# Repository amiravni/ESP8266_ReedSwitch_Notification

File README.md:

# ESP8266_ReedSwitch_Notification

This is a repository for desining a PCB and code for creating an ESP8266 which can be kept alive for months and notify by email when the reed switch changing it state.

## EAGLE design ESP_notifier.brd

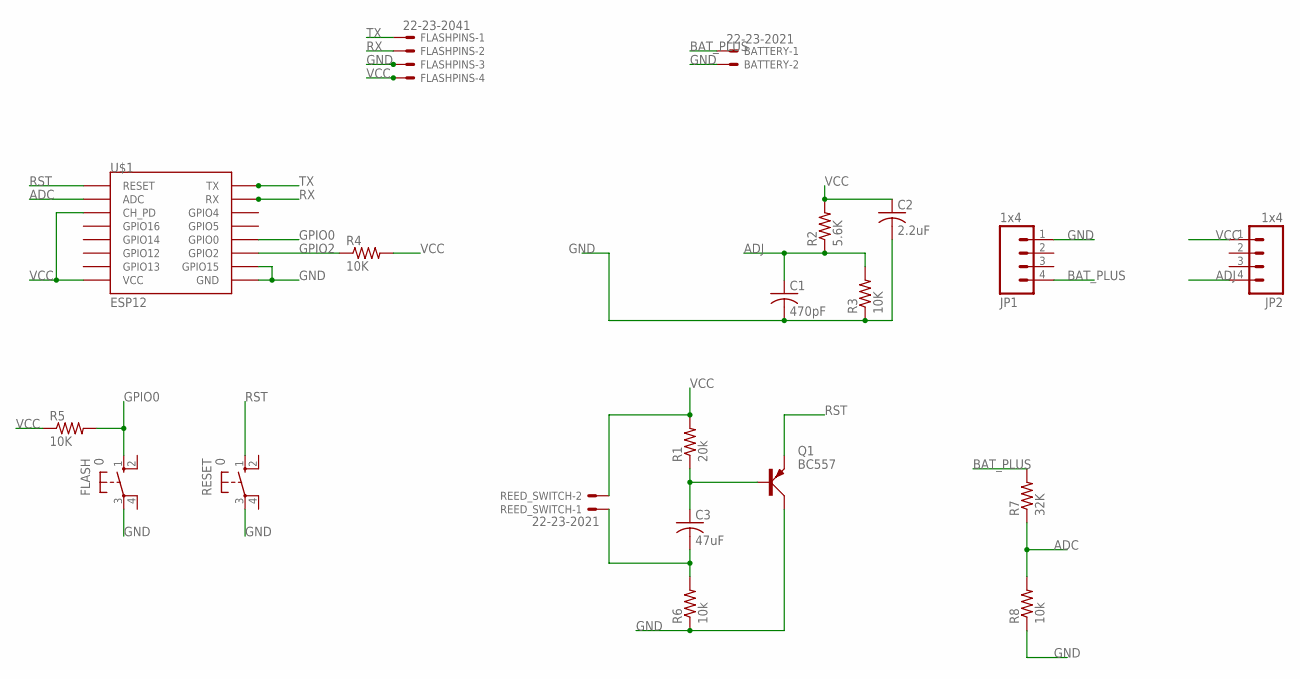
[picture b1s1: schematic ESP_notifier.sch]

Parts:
BATTERY: 22-23-2021
C1: 470pF; C075-032X103
C2: 2.2uF; C075-032X103
C3: 47uF; C075-032X103
FLASH: 0; B3F-10XX
FLASHPINS: 22-23-2041
JP1: 1x4; 1X04_NO_SILK
JP2: 1x4; 1X04_NO_SILK_ALL_ROUND
Q1: BC557; SOT54A
R1: 20k; 0207/9
R2: 5.6K; 0207/9
R3, R4, R5: 10K; 0207/9
R6, R8: 10k; 0207/9
R7: 32K; 0207/9
REED_SWITCH: 22-23-2021
RESET: 0; B3F-10XX
U$1: ESP12

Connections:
ADC: R7.1, R8.2, U$1.ADC
ADJ: C1.1, JP2.4, R2.1, R3.2
BAT_PLUS: BATTERY.1, JP1.4, R7.2
GND: BATTERY.2, C1.2, C2.2, FLASH.3, FLASHPINS.3, JP1.1, Q1.C, R3.1, R6.1, R8.1, RESET.3, U$1.GND, U$1.GPIO15
GPIO0: FLASH.1 (S), R5.2, U$1.GPIO0
GPIO2: R4.1, U$1.GPIO2
unnamed: C3.1, Q1.B, R1.1
unnamed: C3.2, R6.2, REED_SWITCH.1
RST: Q1.E, RESET.1 (S), U$1.RESET
RX: FLASHPINS.2, U$1.RX
TX: FLASHPINS.1, U$1.TX
VCC: C2.1, FLASHPINS.4, JP2.1, R1.2, R2.2, R4.2, R5.1, REED_SWITCH.2, U$1.CH_PD, U$1.VCC

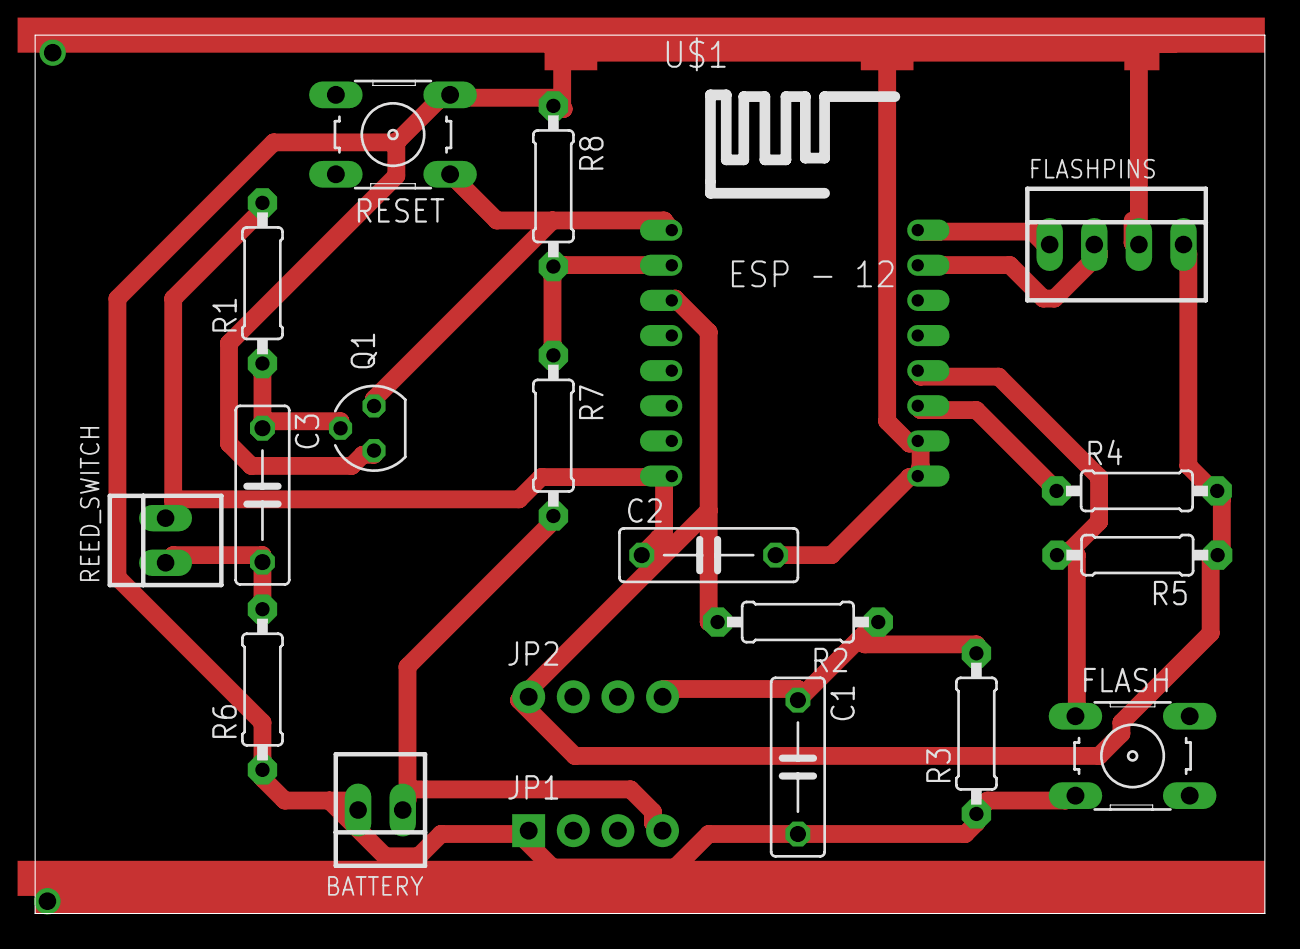
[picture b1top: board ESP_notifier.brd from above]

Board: 2 copper layers, 70.0 x 50.0 mm, 20 parts (0 on the bottom side), 12 nets.

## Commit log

2016-07-17 Add files via upload
    first commit

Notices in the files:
parts and their libraries:
SparkFun-Connectors: Licensing: Creative Commons ShareAlike 4.0 International - https://creativecommons.org/licenses/by-sa/4.0
